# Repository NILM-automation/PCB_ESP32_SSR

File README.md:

# PCB_ESP32_SSR
PCB for the connection between the ESP32-WROOM-32 and a Solid State Relay. The ESP send an activation signal to SSR.

In adition, there is a temperature sensor texas tmp275

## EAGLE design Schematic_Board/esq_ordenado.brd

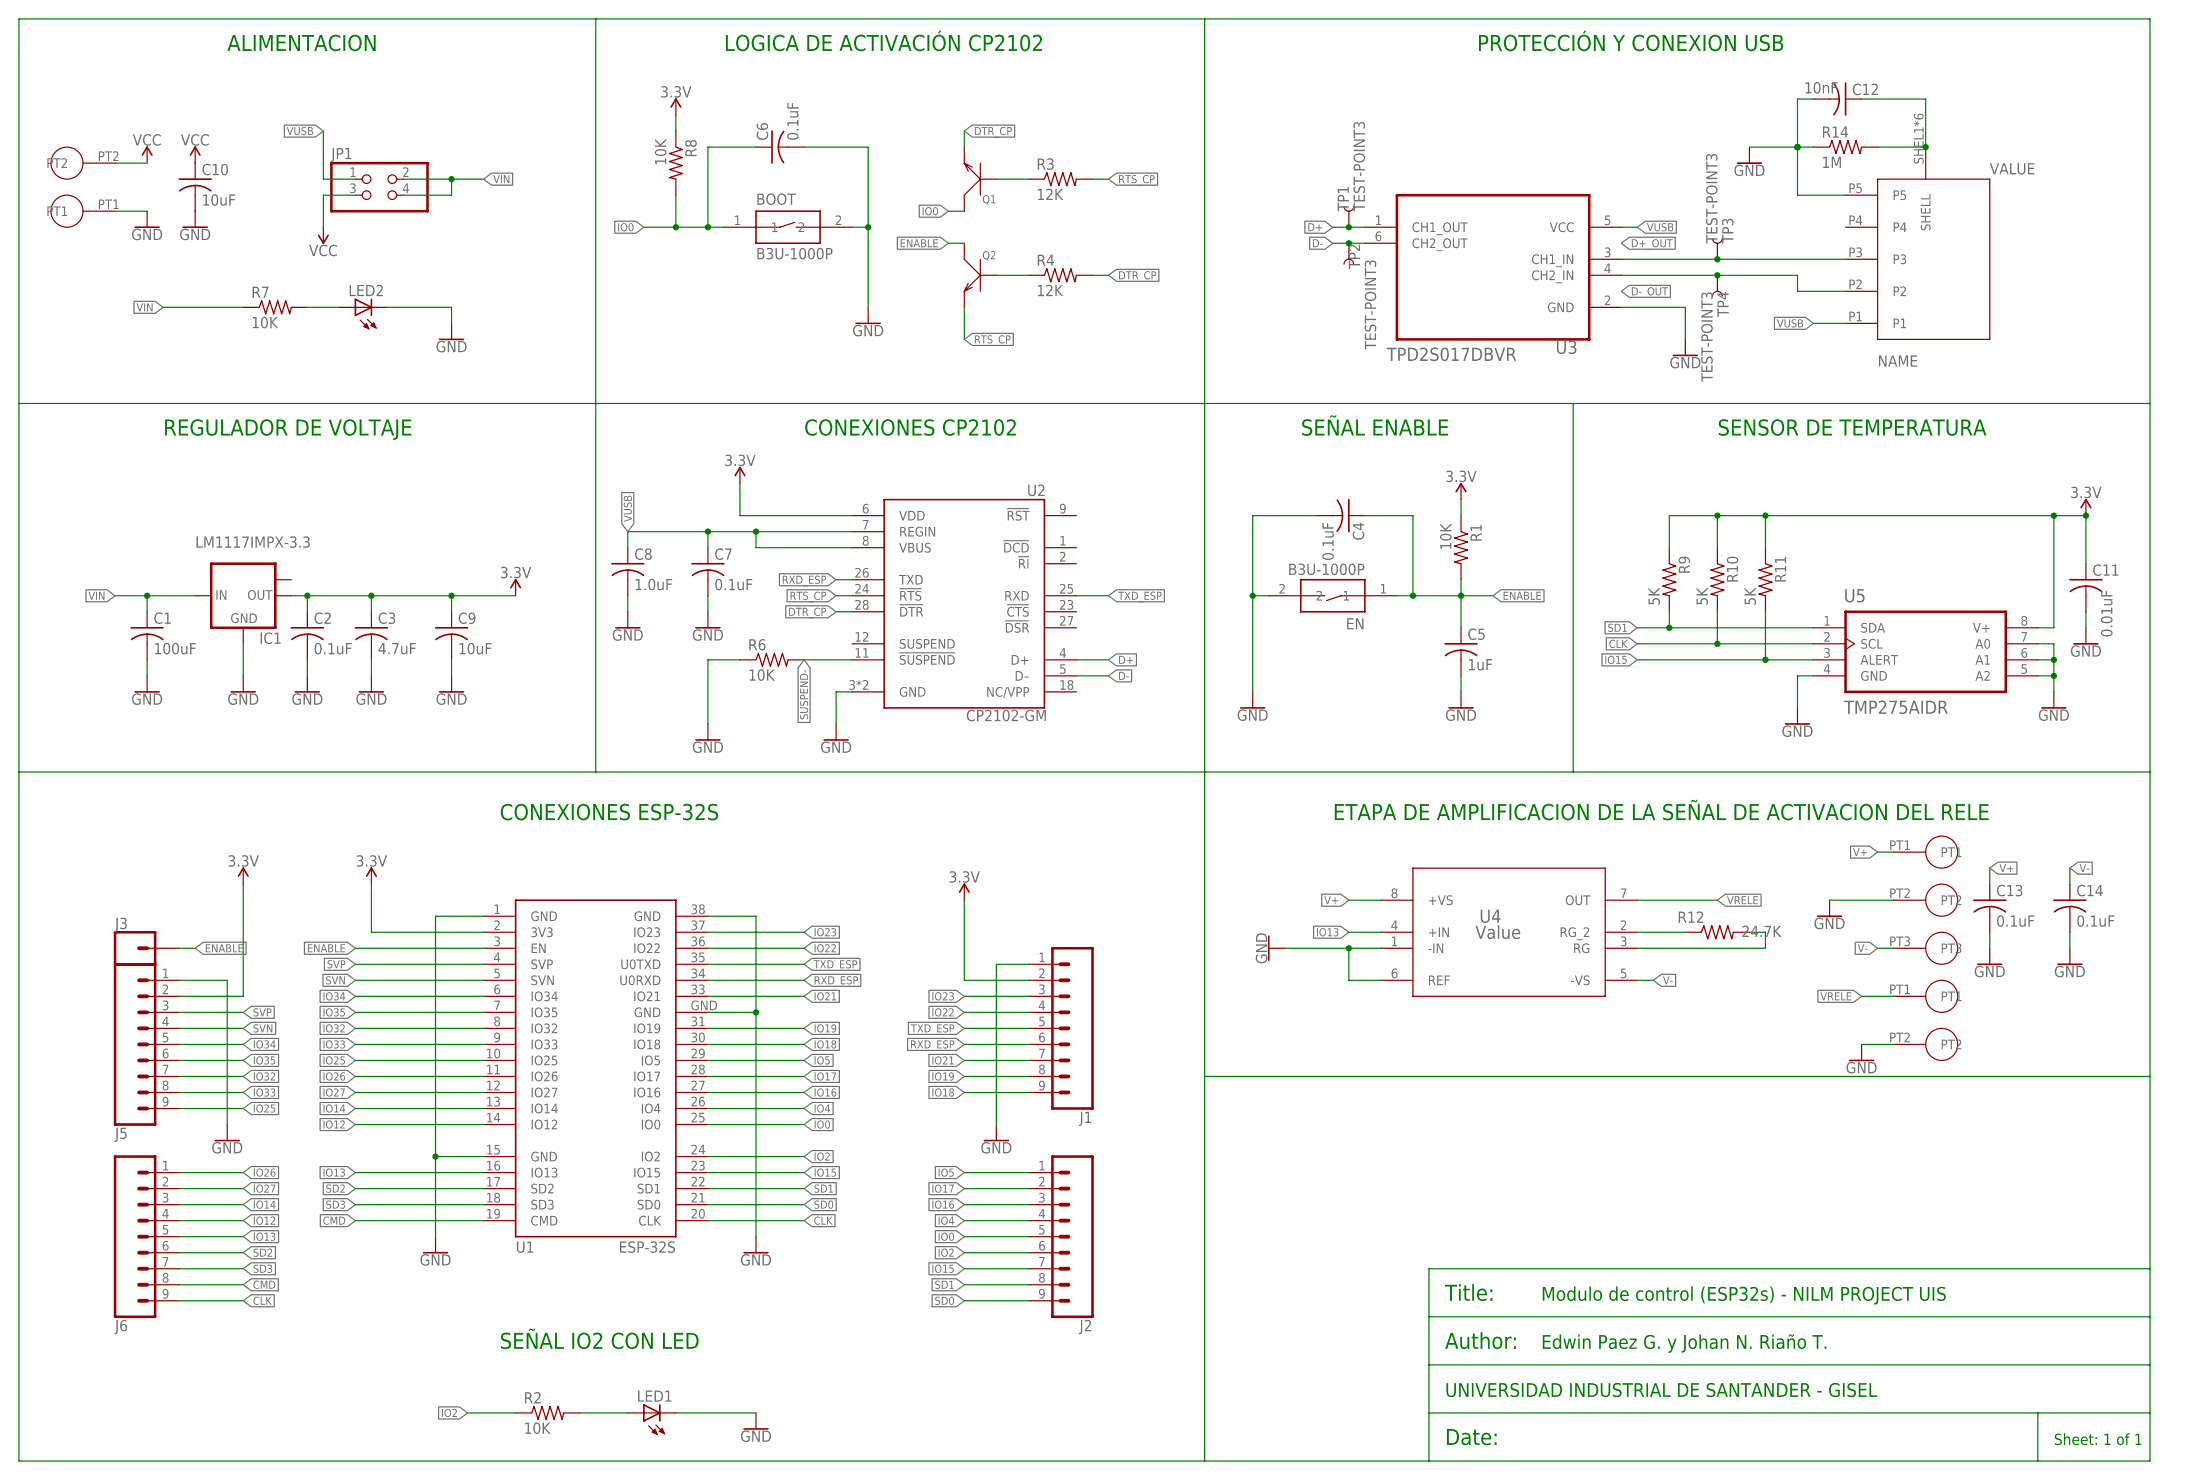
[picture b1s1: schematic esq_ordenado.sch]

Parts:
BOOT: B3U-1000P
C1: 100uF; C0805
C2, C4, C6, C7, C13, C14: 0.1uF; C0805
C3: 4.7uF; C0805
C5: 1uF; C0805
C8: 1.0uF; C0805
C9, C10: 10uF; C0805
C11: 0.01uF; C0805
C12: 10nF; C0805
EN: B3U-1000P
IC1: LM1117IMPX-3.3; SOT223
J1, J2, J5, J6: CONN_09; 1X09
J3: CONN_01; 1X01
JP1: PINHD-2X2; 2X02
LED1, LED2: LEDCHIPLED_0805; CHIPLED_0805
Q1, Q2: SMD-TRANSISTORS-NPN-25V-500MW(SOT-23); SOT-23
R1, R2, R6, R7, R8: 10K; R0805
R3, R4: 12K; R0805
R9, R10, R11: 5K; R0805
R12: 24.7K; R0805
R14: 1M; R0805
TP1, TP2, TP3, TP4: TEST-POINT3; PAD.03X.03
U1: ESP-32S
U2: CP2102-GM; QFN50P500X500X100-29N
U3: TPD2S017DBVR; SOT95P280X145-6N
U4: Value; D0008A_M
U5: TMP275AIDR
U$1: MICRO_USB_B-AMPHENOL(10118192); MICRO_B_10118192
U$2, U$3: PT2,5/2-5,0
U$4: PT2,5/3-5,0

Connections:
3.3V: C2.1, C3.1, C9.1, C11.1, IC1.2 (OUT), J1.2, J5.2, R1.1, R8.1, R9.1, R10.1, R11.1, U1.2 (3V3), U2.6 (VDD), U5.8 (V+)
CLK: J6.9, R10.2, U1.20 (CLK), U5.2 (SCL)
CMD: J6.8, U1.19 (CMD)
D+: TP1.P$1, U2.4 (D+), U3.1 (CH1_OUT)
D+_OUT: TP3.P$1, U3.3 (CH1_IN), U$1.P3
D-: TP2.P$1, U2.5 (D–), U3.6 (CH2_OUT)
D-_OUT: TP4.P$1, U3.4 (CH2_IN), U$1.P2
DTR_CP: Q1.2 (E), R4.2, U2.28 (!DTR)
ENABLE: C4.1, C5.1, EN.1, J3.1, Q2.3 (C), R1.2, U1.3 (EN)
GND: BOOT.2, C1.2, C2.2, C3.2, C4.2, C5.2, C6.2, C7.2, C8.2, C9.2, C10.2, C11.2, C12.2, C13.2, C14.2, EN.2, IC1.1 (GND), J1.1, J5.1, LED1.C, LED2.C, R6.1, R14.1, U1.1 (GND), U1.15 (GND), U1.38 (GND), U1.GND, U2.3 (GND), U2.29 (GND), U3.2 (GND), U4.1 (-IN), U4.6 (REF), U5.4 (GND), U5.5 (A2), U5.6 (A1), U5.7 (A0), U$1.P5, U$2.PT1, U$3.PT2, U$4.PT2
IO0: BOOT.1, C6.1, J2.5, Q1.3 (C), R8.2, U1.25 (IO0)
IO2: J2.6, R2.1, U1.24 (IO2)
IO4: J2.4, U1.26 (IO4)
IO5: J2.1, U1.29 (IO5)
IO12: J6.4, U1.14 (IO12)
IO13: J6.5, U1.16 (IO13), U4.4 (+IN)
IO14: J6.3, U1.13 (IO14)
IO15: J2.7, R11.2, U1.23 (IO15), U5.3 (ALERT)
IO16: J2.3, U1.27 (IO16)
IO17: J2.2, U1.28 (IO17)
IO18: J1.9, U1.30 (IO18)
IO19: J1.8, U1.31 (IO19)
IO21: J1.7, U1.33 (IO21)
IO22: J1.4, U1.36 (IO22)
IO23: J1.3, U1.37 (IO23)
IO25: J5.9, U1.10 (IO25)
IO26: J6.1, U1.11 (IO26)
IO27: J6.2, U1.12 (IO27)
IO32: J5.7, U1.8 (IO32)
IO33: J5.8, U1.9 (IO33)
IO34: J5.5, U1.6 (IO34)
IO35: J5.6, U1.7 (IO35)
unnamed: LED1.A, R2.2
unnamed: Q1.1 (B), R3.1
unnamed: Q2.1 (B), R4.1
unnamed: LED2.A, R7.2
unnamed: C12.1, R14.2, U$1.SHEL1 (SHELL), U$1.SHEL2 (SHELL), U$1.SHEL3 (SHELL), U$1.SHEL4 (SHELL), U$1.SHEL5 (SHELL), U$1.SHEL6 (SHELL)
unnamed: R12.1, U4.2 (RG_2)
unnamed: R12.2, U4.3 (RG)
RTS_CP: Q2.2 (E), R3.2, U2.24 (!RTS)
RXD_ESP: J1.6, U1.34 (U0RXD), U2.26 (TXD)
SD0: J2.9, U1.21 (SD0)
SD1: J2.8, R9.2, U1.22 (SD1), U5.1 (SDA)
SD2: J6.6, U1.17 (SD2)
SD3: J6.7, U1.18 (SD3)
SUSPEND-: R6.2, U2.11 (!SUSPEND)
SVN: J5.4, U1.5 (SVN)
SVP: J5.3, U1.4 (SVP)
TXD_ESP: J1.5, U1.35 (U0TXD), U2.25 (RXD)
V+: C13.1, U4.8 (+VS), U$4.PT1
V-: C14.1, U4.5 (-VS), U$4.PT3
VCC: C10.1, JP1.3, U$2.PT2
VIN: C1.1, IC1.3 (IN), JP1.2, JP1.4, R7.1
VRELE: U4.7 (OUT), U$3.PT1
VUSB: C7.1, C8.1, JP1.1, U2.7 (REGIN), U2.8 (VBUS), U3.5 (VCC), U$1.P1

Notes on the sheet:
REGULADOR DE VOLTAJE
SEÑAL ENABLE
CONEXIONES ESP-32S
SEÑAL IO2 CON LED
LOGICA DE ACTIVACIÓN CP2102
CONEXIONES CP2102
PROTECCIÓN Y CONEXION USB
ALIMENTACION
SENSOR DE TEMPERATURA
ETAPA DE AMPLIFICACION DE LA SEÑAL DE ACTIVACION DEL RELE
Modulo de control (ESP32s) - NILM PROJECT UIS
Title:
Author:
Edwin Paez G. y Johan N. Riaño T.
UNIVERSIDAD INDUSTRIAL DE SANTANDER - GISEL
Sheet: 1 of 1
Date:

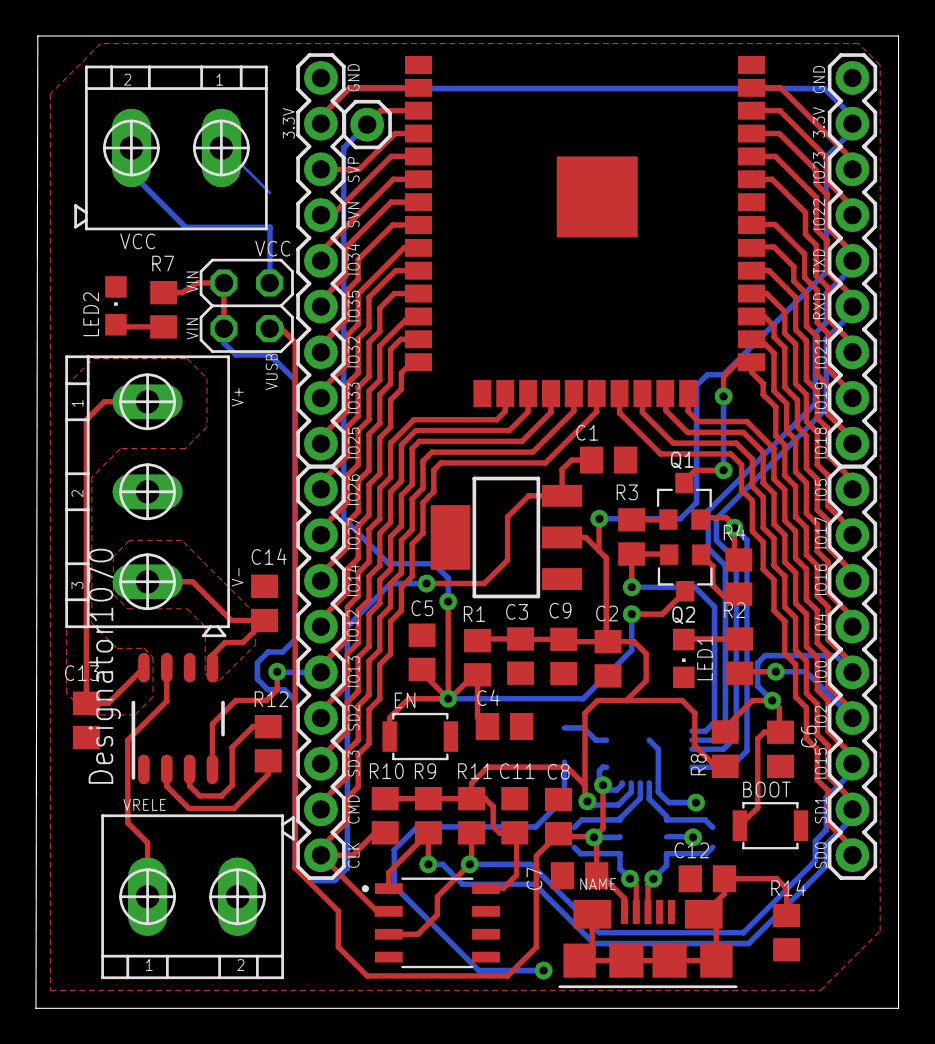
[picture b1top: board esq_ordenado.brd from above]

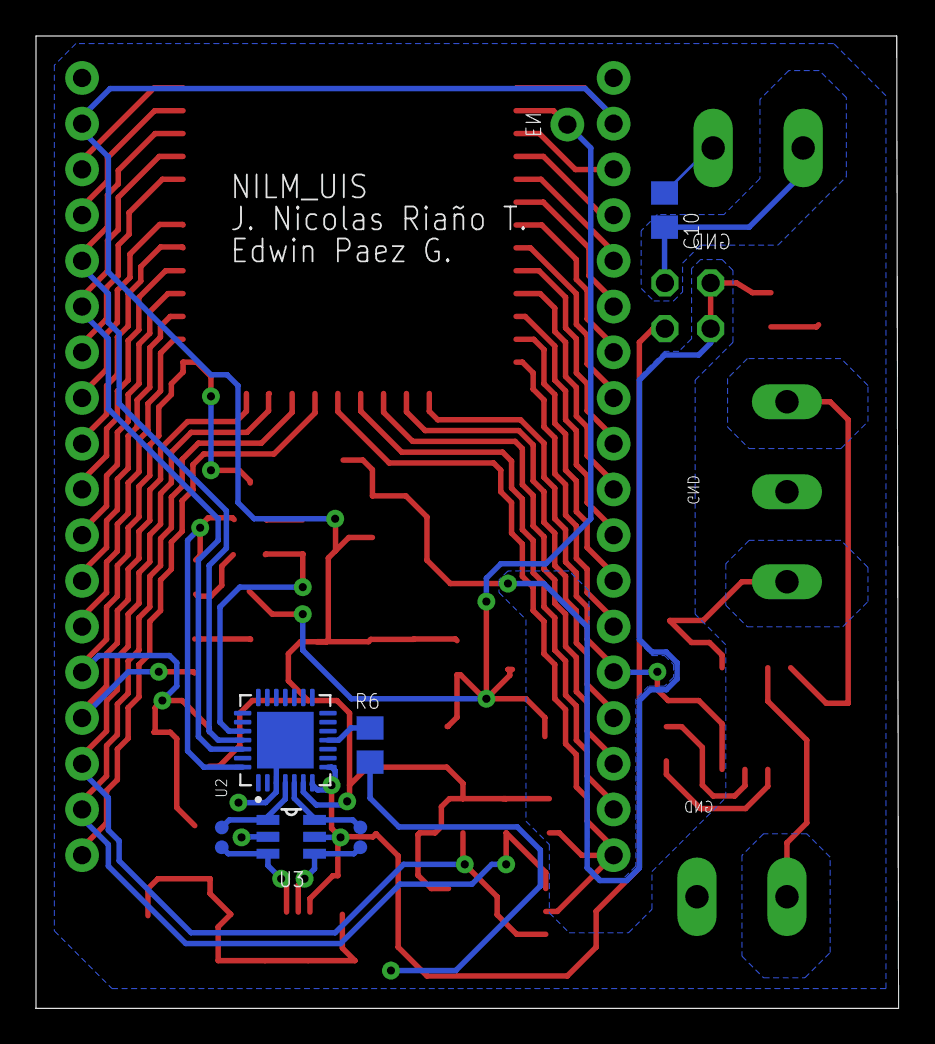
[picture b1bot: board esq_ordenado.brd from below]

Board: 2 copper layers, 47.9 x 54.0 mm, 52 parts (8 on the bottom side), 55 nets.

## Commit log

2019-12-14 incluyendo directorios y primer avance de la PCB
2019-12-16 Adicionando Datasheet TPD2S017 y conexiones entre D+ y D- a la regleta
2019-12-17 Correcciones D+ Y D- en TPD2S017 y en los pines, para un mejor ruteo
2019-12-18 PCB terminada cumpliendo la mayoria de normas
2020-04-22 pcb segunda version terminada
2020-05-02 actualizacion de datahseets, lista de elementos, esquematico terminado
2020-05-05 corrección footprint switch tactile y borrado de pistas de la board
2020-05-11 actualizacion de files/Schematic/Board/Datasheet..
2020-05-19 Nuevos switch, option1 D+ D-
2020-05-26 Version final-revision nicolas
2020-05-29 Correc Borneras - revision nicolas
2020-05-31 centrar PCB - revision nicolas
2020-05-31 Lista elementos terminada - revision nicolas
2020-05-31 actualizacion file Eagle_libraries
2020-06-04 DRC Y ERC CHECK - revision nicolas

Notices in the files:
parts and their libraries:
SparkFun-PowerSymbols: Licensing: Creative Commons ShareAlike 4.0 International - https://creativecommons.org/licenses/by-sa/4.0
esp32: Creative Commons Attribution-ShareAlike 4.0 International
